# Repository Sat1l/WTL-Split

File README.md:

# WTL-Split

[pics](https://imgur.com/a/rFJwc3o)

take this project as is

not tested and no firmware

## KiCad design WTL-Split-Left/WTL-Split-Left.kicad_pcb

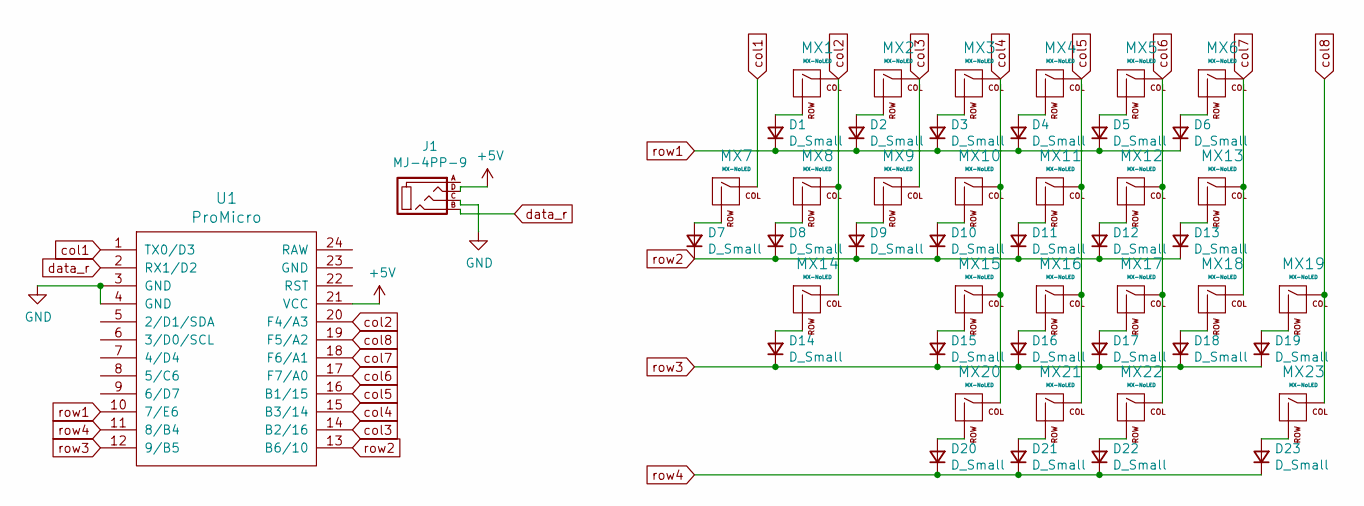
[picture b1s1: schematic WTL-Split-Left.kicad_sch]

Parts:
D1, D2, D3, D4, D5, D6, D7, D8, D9, D10, D11, D12, D13, D14, D15, D16, D17, D18, D19, D20, D21, D22, D23: D_Small; D3_SMD_v2
J1: MJ-4PP-9; MJ-4PP-9_1side
MX1, MX2, MX3, MX4, MX5, MX6, MX7, MX8, MX9, MX10, MX11, MX12, MX13, MX15, MX16, MX17, MX18, MX19, MX20, MX21, MX23: MX-NoLED; MXOnly-1U-NoLED
MX14: MX-NoLED; MXOnly-2.25U-ReversedStabilizers-NoLED
MX22: MX-NoLED; MXOnly-2U-ReversedStabilizers-NoLED
U1: ProMicro; ProMicro_v3

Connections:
+5V: J1.D, U1.21 (VCC)
GND: J1.C, U1.3 (GND), U1.4 (GND)
unnamed: D1.2 (A), MX1.2 (ROW)
unnamed: D2.2 (A), MX2.2 (ROW)
unnamed: D3.2 (A), MX3.2 (ROW)
unnamed: D4.2 (A), MX4.2 (ROW)
unnamed: D5.2 (A), MX5.2 (ROW)
unnamed: D6.2 (A), MX6.2 (ROW)
unnamed: D7.2 (A), MX7.2 (ROW)
unnamed: D8.2 (A), MX8.2 (ROW)
unnamed: D9.2 (A), MX9.2 (ROW)
unnamed: D10.2 (A), MX10.2 (ROW)
unnamed: D11.2 (A), MX11.2 (ROW)
unnamed: D12.2 (A), MX12.2 (ROW)
unnamed: D13.2 (A), MX13.2 (ROW)
unnamed: D14.2 (A), MX14.2 (ROW)
unnamed: D15.2 (A), MX15.2 (ROW)
unnamed: D16.2 (A), MX16.2 (ROW)
unnamed: D17.2 (A), MX17.2 (ROW)
unnamed: D18.2 (A), MX18.2 (ROW)
unnamed: D19.2 (A), MX19.2 (ROW)
unnamed: D20.2 (A), MX20.2 (ROW)
unnamed: D21.2 (A), MX21.2 (ROW)
unnamed: D22.2 (A), MX22.2 (ROW)
unnamed: D23.2 (A), MX23.2 (ROW)
col1: MX7.1 (COL), U1.1 (TX0/D3)
col2: MX1.1 (COL), MX8.1 (COL), MX14.1 (COL), U1.20 (F4/A3)
col3: MX2.1 (COL), MX9.1 (COL), U1.14 (B2/16)
col4: MX3.1 (COL), MX10.1 (COL), MX15.1 (COL), MX20.1 (COL), U1.15 (B3/14)
col5: MX4.1 (COL), MX11.1 (COL), MX16.1 (COL), MX21.1 (COL), U1.16 (B1/15)
col6: MX5.1 (COL), MX12.1 (COL), MX17.1 (COL), MX22.1 (COL), U1.17 (F7/A0)
col7: MX6.1 (COL), MX13.1 (COL), MX18.1 (COL), U1.18 (F6/A1)
col8: MX19.1 (COL), MX23.1 (COL), U1.19 (F5/A2)
data_r: J1.B, U1.2 (RX1/D2)
row1: D1.1 (K), D2.1 (K), D3.1 (K), D4.1 (K), D5.1 (K), D6.1 (K), U1.10 (7/E6)
row2: D7.1 (K), D8.1 (K), D9.1 (K), D10.1 (K), D11.1 (K), D12.1 (K), D13.1 (K), U1.13 (B6/10)
row3: D14.1 (K), D15.1 (K), D16.1 (K), D17.1 (K), D18.1 (K), D19.1 (K), U1.12 (9/B5)
row4: D20.1 (K), D21.1 (K), D22.1 (K), D23.1 (K), U1.11 (8/B4)

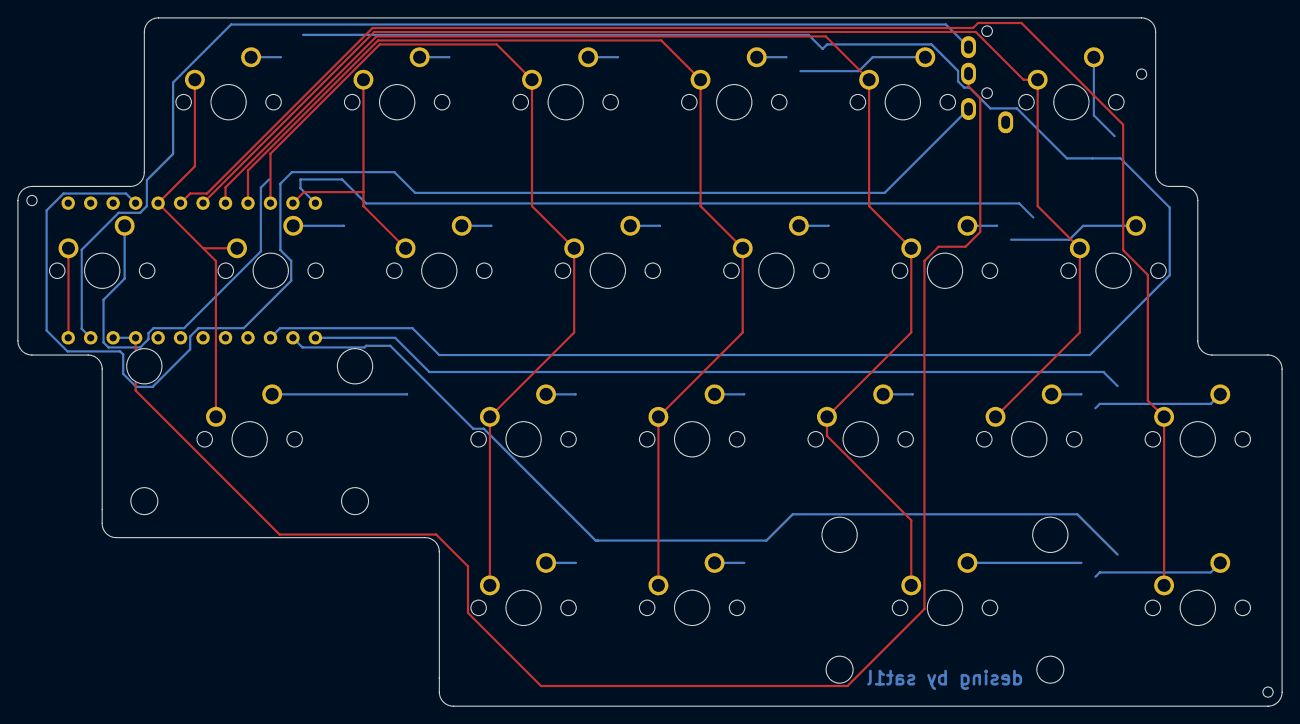
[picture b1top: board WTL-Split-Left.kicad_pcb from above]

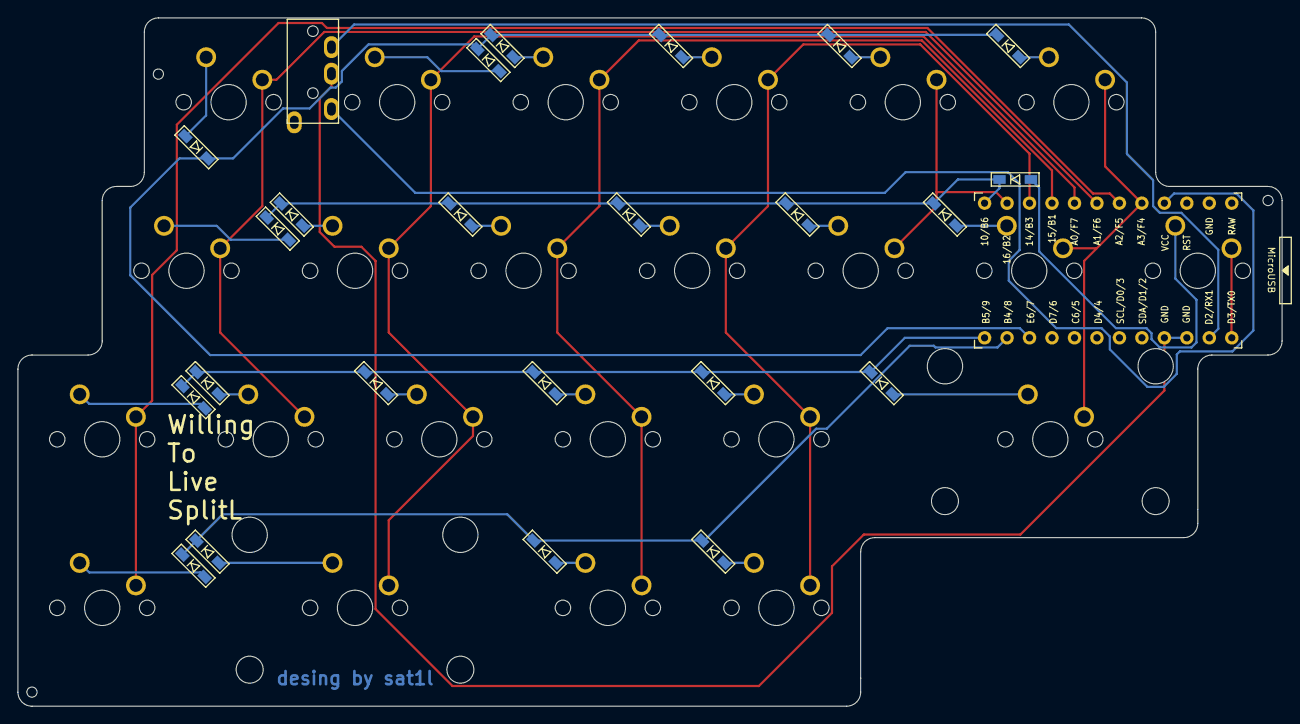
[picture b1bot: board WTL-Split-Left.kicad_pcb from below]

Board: 2 copper layers, 142.9 x 77.8 mm, 48 parts (25 on the bottom side), 38 nets.

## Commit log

2021-09-05 this project gonna end up in a bin but ok
2021-09-05 i'm fucking tired
2021-09-05 close to complete
2021-09-05 wtf idk what i've done but now its better
2021-09-11 1.0 version
2021-12-28 I don't remember what i've done
2021-12-28 changes shift key on left half from 2u to 2.25u
2021-12-28 yeah
2022-06-01 tf i did?
